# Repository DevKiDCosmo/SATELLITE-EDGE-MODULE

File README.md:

# SATELLITE-EDGE-MODULE
A satellite edge module ready for competition

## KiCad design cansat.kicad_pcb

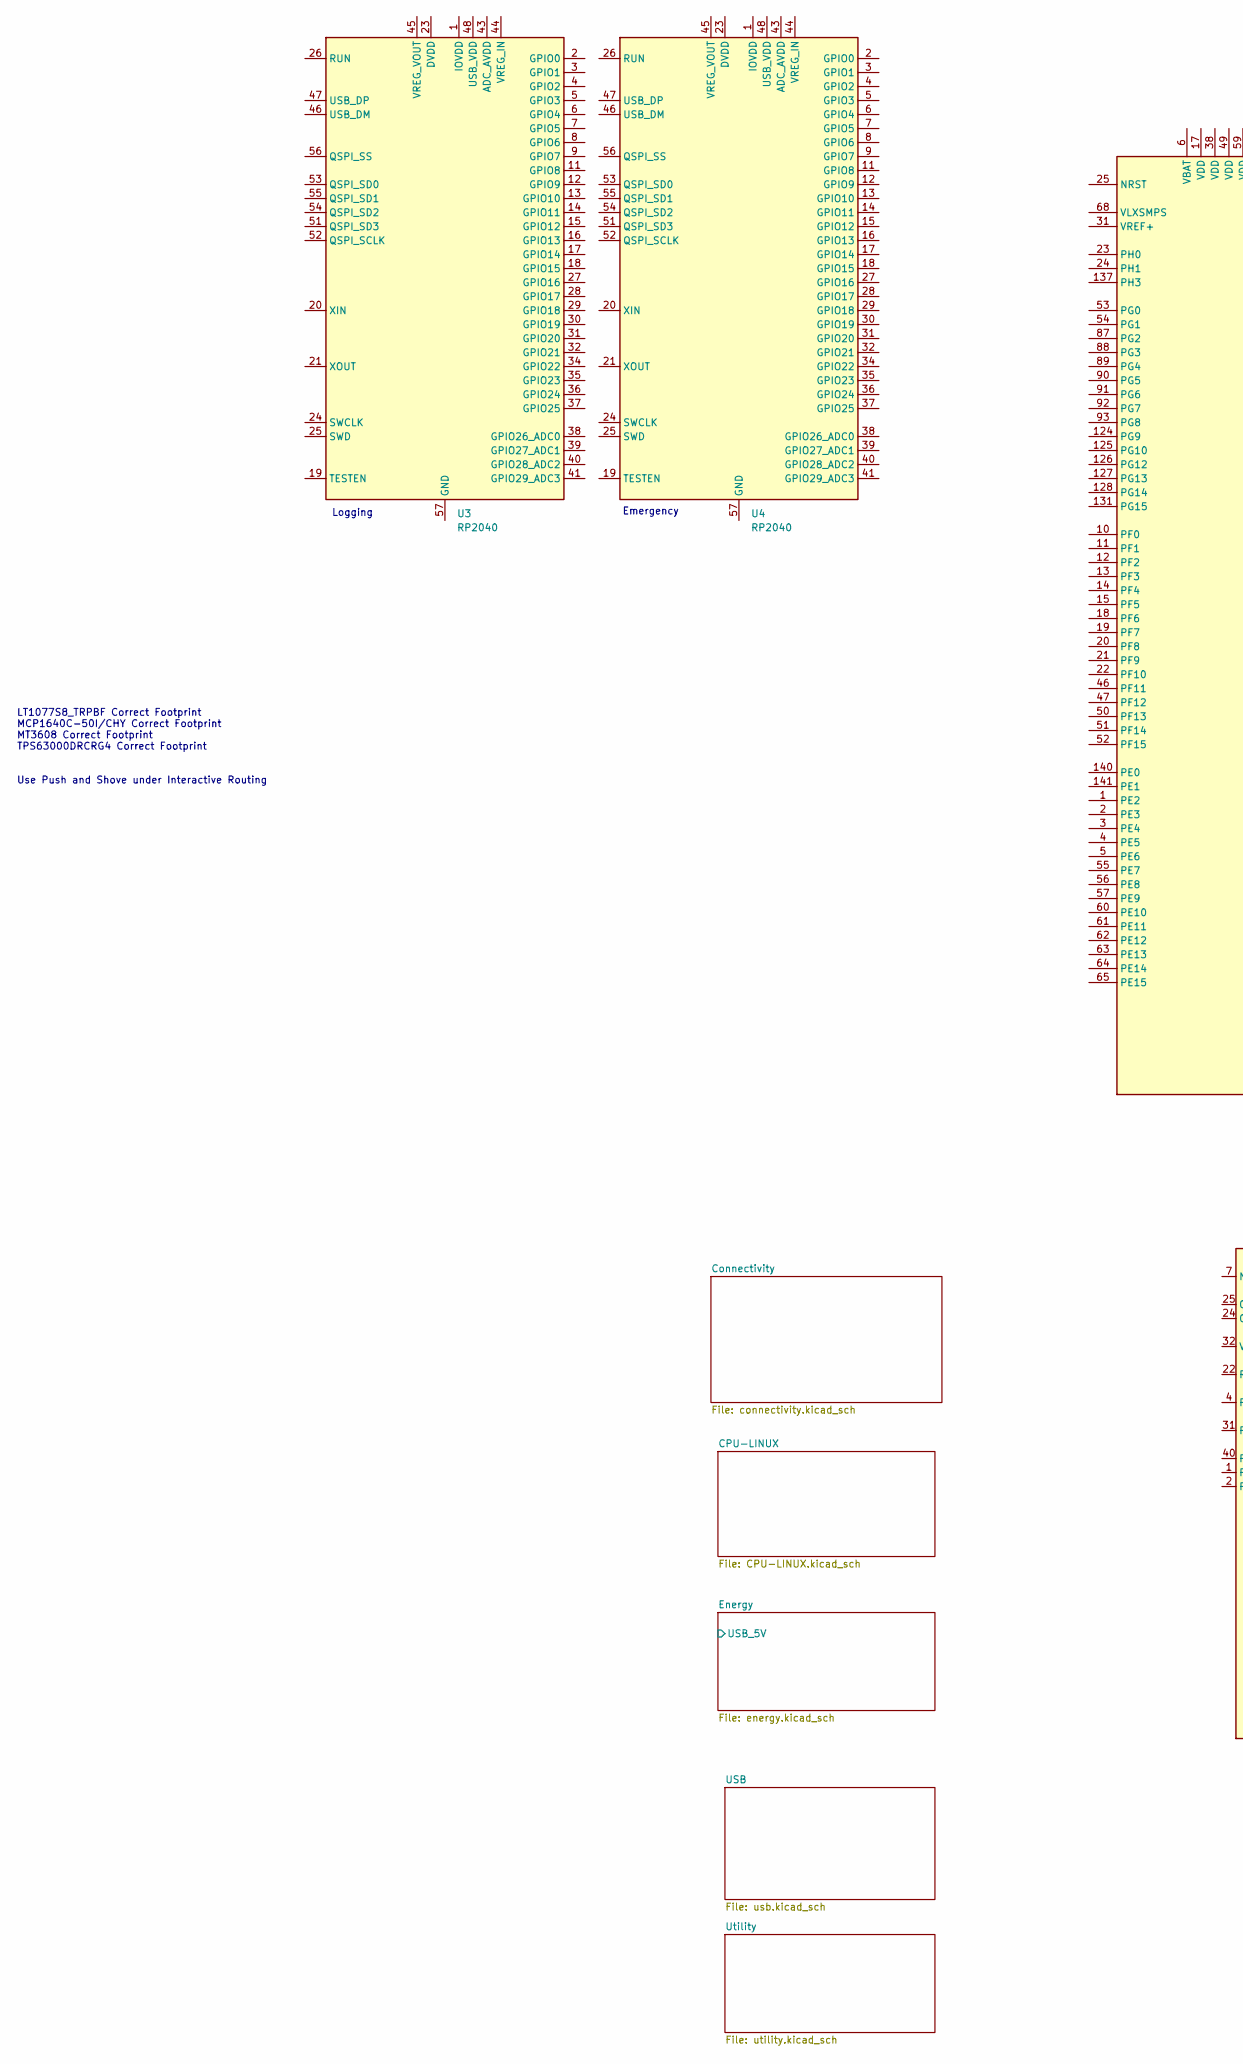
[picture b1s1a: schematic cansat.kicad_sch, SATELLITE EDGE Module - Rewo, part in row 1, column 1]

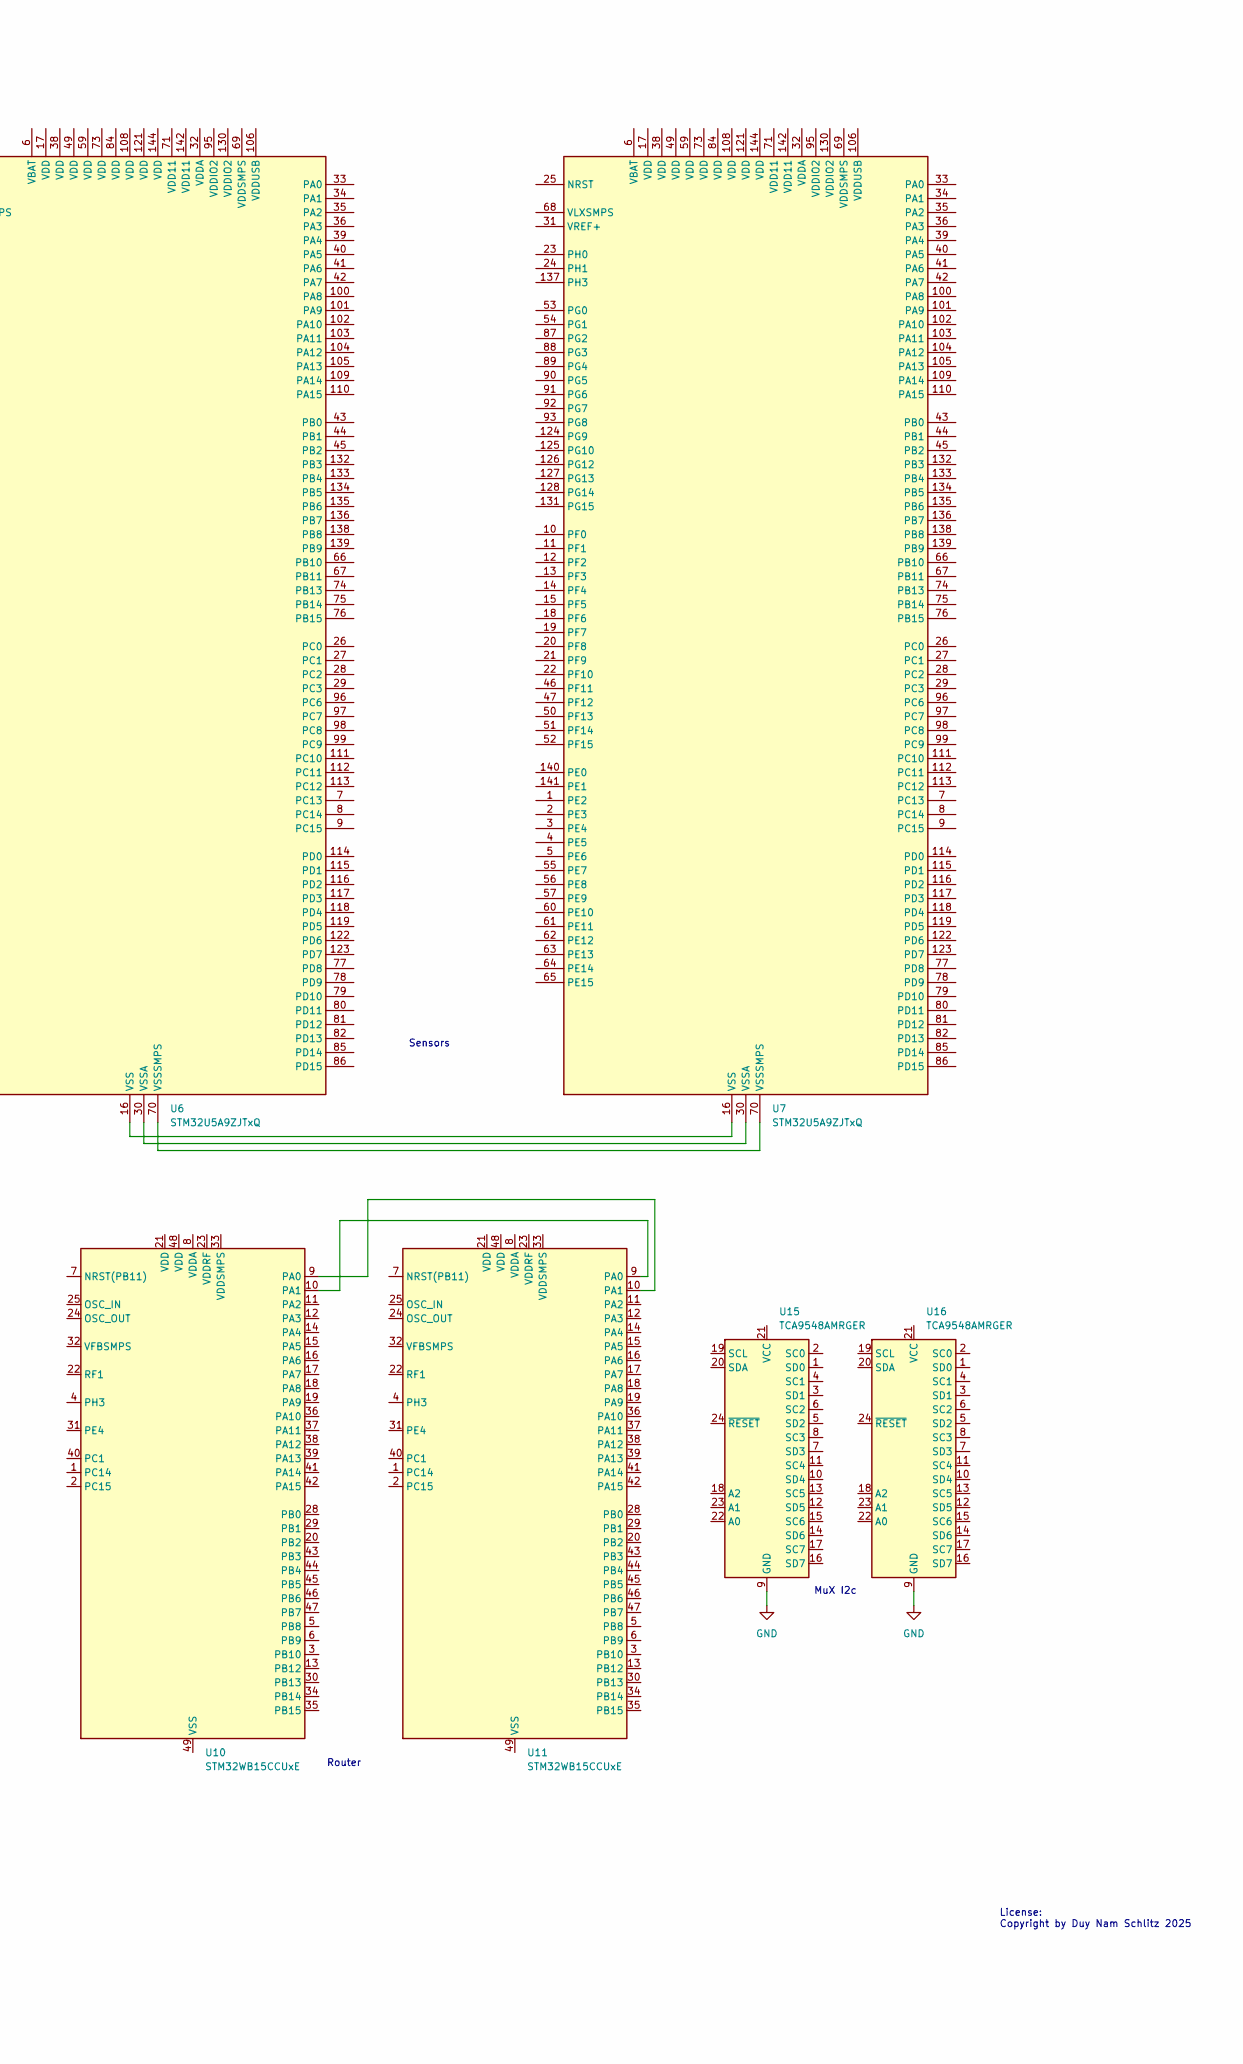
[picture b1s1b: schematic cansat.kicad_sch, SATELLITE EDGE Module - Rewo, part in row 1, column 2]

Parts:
U3, U4: RP2040; QFN-56-1EP_7x7mm_P0.4mm_EP3.2x3.2mm
U6, U7: STM32U5A9ZJTxQ; LQFP-144_20x20mm_P0.5mm
U10, U11: STM32WB15CCUxE; QFN-48-1EP_7x7mm_P0.5mm_EP5.6x5.6mm
U15, U16: TCA9548AMRGER; Texas_RGE0024C_VQFN-24-1EP_4x4mm_P0.5mm_EP2.1x2.1mm

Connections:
GND: U15.9 (GND), U16.9 (GND); also elsewhere on the board
unnamed: U3.23 (DVDD), U3.50 (DVDD)
unnamed: U3.1 (IOVDD), U3.10 (IOVDD), U3.22 (IOVDD), U3.33 (IOVDD), U3.42 (IOVDD), U3.49 (IOVDD)
unnamed: U4.23 (DVDD), U4.50 (DVDD)
unnamed: U4.1 (IOVDD), U4.10 (IOVDD), U4.22 (IOVDD), U4.33 (IOVDD), U4.42 (IOVDD), U4.49 (IOVDD)
unnamed: U6.16 (VSS), U6.37 (VSS), U6.48 (VSS), U6.58 (VSS), U6.72 (VSS), U6.83 (VSS), U6.94 (VSS), U6.107 (VSS), U6.120 (VSS), U6.129 (VSS), U6.143 (VSS), U7.16 (VSS), U7.37 (VSS), U7.48 (VSS), U7.58 (VSS), U7.72 (VSS), U7.83 (VSS), U7.94 (VSS), U7.107 (VSS), U7.120 (VSS), U7.129 (VSS), U7.143 (VSS)
unnamed: U6.30 (VSSA), U7.30 (VSSA)
unnamed: U6.70 (VSSSMPS), U7.70 (VSSSMPS)
unnamed: U10.9 (PA0), U11.10 (PA1)
unnamed: U10.10 (PA1), U11.9 (PA0)

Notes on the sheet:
Logging
Sensors
License: Copyright by Duy Nam Schlitz 2025
MuX I2c
LT1077S8_TRPBF Correct Footprint MCP1640C-50I/CHY Correct Footprint MT3608 Correct Footprint TPS63000DRCRG4 Correct Footprint Use Push and Shove under Interactive Routing
Router
Emergency

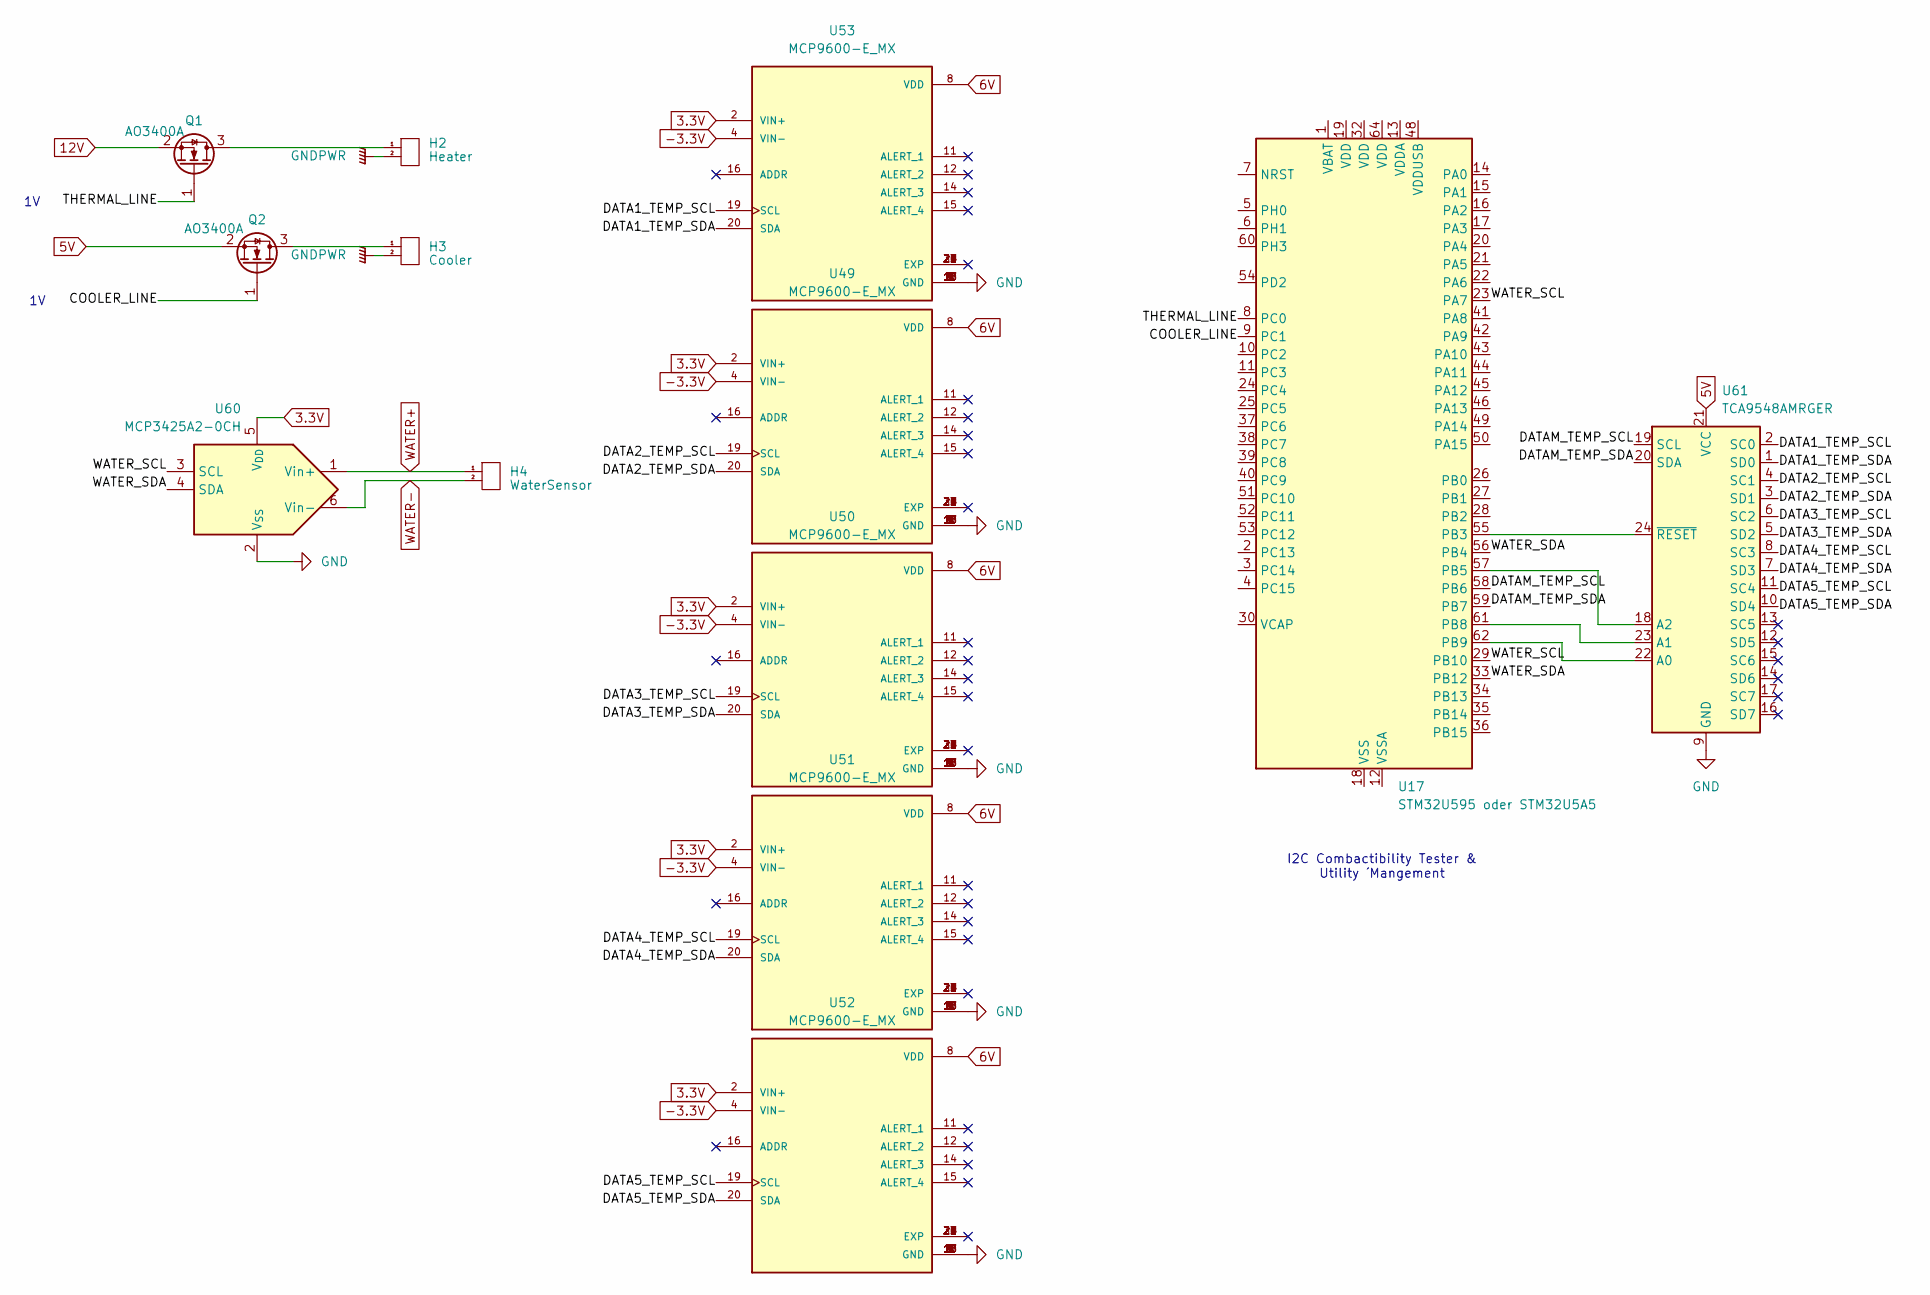
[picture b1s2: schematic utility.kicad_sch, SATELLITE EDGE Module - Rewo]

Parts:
H2: Heater; PinHeader_1x02_P2.54mm_Vertical
H3: Cooler; PinHeader_1x02_P2.54mm_Vertical
H4: WaterSensor; PinHeader_1x02_P2.54mm_Vertical
Q1, Q2: AO3400A; SOT-23
U17: STM32U595 oder STM32U5A5; LQFP-64_10x10mm_P0.5mm
U49, U50, U51, U52, U53: MCP9600-E_MX; QFN65P500X500X100-21N_MCP9600-E_MX; PARTREV F
U60: MCP3425A2-0CH; SOT-23-6
U61: TCA9548AMRGER; Texas_RGE0024C_VQFN-24-1EP_4x4mm_P0.5mm_EP2.1x2.1mm

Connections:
3.3V: U49.2 (VIN+), U50.2 (VIN+), U51.2 (VIN+), U52.2 (VIN+), U53.2 (VIN+), U60.5 (V_{DD}); also elsewhere on the board
5V: Q2.2 (S), U61.21 (VCC); also elsewhere on the board
6V: U49.8 (VDD), U50.8 (VDD), U51.8 (VDD), U52.8 (VDD), U53.8 (VDD); also elsewhere on the board
12V: Q1.2 (S); also elsewhere on the board
-3.3V: U49.4 (VIN-), U50.4 (VIN-), U51.4 (VIN-), U52.4 (VIN-), U53.4 (VIN-); also elsewhere on the board
/Utility/COOLER_LINE: Q2.1 (G), U17.9 (PC1)
/Utility/DATA1_TEMP_SCL: U53.19 (SCL), U61.2 (SC0)
/Utility/DATA1_TEMP_SDA: U53.20 (SDA), U61.1 (SD0)
/Utility/DATA2_TEMP_SCL: U49.19 (SCL), U61.4 (SC1)
/Utility/DATA2_TEMP_SDA: U49.20 (SDA), U61.3 (SD1)
/Utility/DATA3_TEMP_SCL: U50.19 (SCL), U61.6 (SC2)
/Utility/DATA3_TEMP_SDA: U50.20 (SDA), U61.5 (SD2)
/Utility/DATA4_TEMP_SCL: U51.19 (SCL), U61.8 (SC3)
/Utility/DATA4_TEMP_SDA: U51.20 (SDA), U61.7 (SD3)
/Utility/DATA5_TEMP_SCL: U52.19 (SCL), U61.11 (SC4)
/Utility/DATA5_TEMP_SDA: U52.20 (SDA), U61.10 (SD4)
/Utility/DATAM_TEMP_SCL: U17.58 (PB6), U61.19 (SCL)
/Utility/DATAM_TEMP_SDA: U17.59 (PB7), U61.20 (SDA)
/Utility/THERMAL_LINE: Q1.1 (G), U17.8 (PC0)
/Utility/WATER_SCL: U17.23 (PA7), U17.29 (PB10), U60.3 (SCL)
/Utility/WATER_SDA: U17.33 (PB12), U17.56 (PB4), U60.4 (SDA)
GND: U49.1 (GND), U49.3 (GND), U49.5 (GND), U49.6 (GND), U49.7 (GND), U49.9 (GND), U49.10 (GND), U49.13 (GND), U49.17 (GND), U49.18 (GND), U50.1 (GND), U50.3 (GND), U50.5 (GND), U50.6 (GND), U50.7 (GND), U50.9 (GND), U50.10 (GND), U50.13 (GND), U50.17 (GND), U50.18 (GND), U51.1 (GND), U51.3 (GND), U51.5 (GND), U51.6 (GND), U51.7 (GND), U51.9 (GND), U51.10 (GND), U51.13 (GND), U51.17 (GND), U51.18 (GND), U52.1 (GND), U52.3 (GND), U52.5 (GND), U52.6 (GND), U52.7 (GND), U52.9 (GND), U52.10 (GND), U52.13 (GND), U52.17 (GND), U52.18 (GND), U53.1 (GND), U53.3 (GND), U53.5 (GND), U53.6 (GND), U53.7 (GND), U53.9 (GND), U53.10 (GND), U53.13 (GND), U53.17 (GND), U53.18 (GND), U60.2 (V_{SS}), U61.9 (GND); also elsewhere on the board
GNDPWR: H2.2, H3.2; also elsewhere on the board
unnamed: H2.1, Q1.3 (D)
unnamed: H3.1, Q2.3 (D)
unnamed: U17.55 (PB3), U61.24 (~RESET)
unnamed: U17.57 (PB5), U61.18 (A2)
unnamed: U17.61 (PB8), U61.23 (A1)
unnamed: U17.62 (PB9), U61.22 (A0)
unnamed: U17.18 (VSS), U17.31 (VSS), U17.47 (VSS), U17.63 (VSS)
WATER+: H4.1, U60.1 (Vin+); also elsewhere on the board
WATER-: H4.2, U60.6 (Vin-); also elsewhere on the board

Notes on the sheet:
I2C Combactibility Tester & Utility ´Mangement

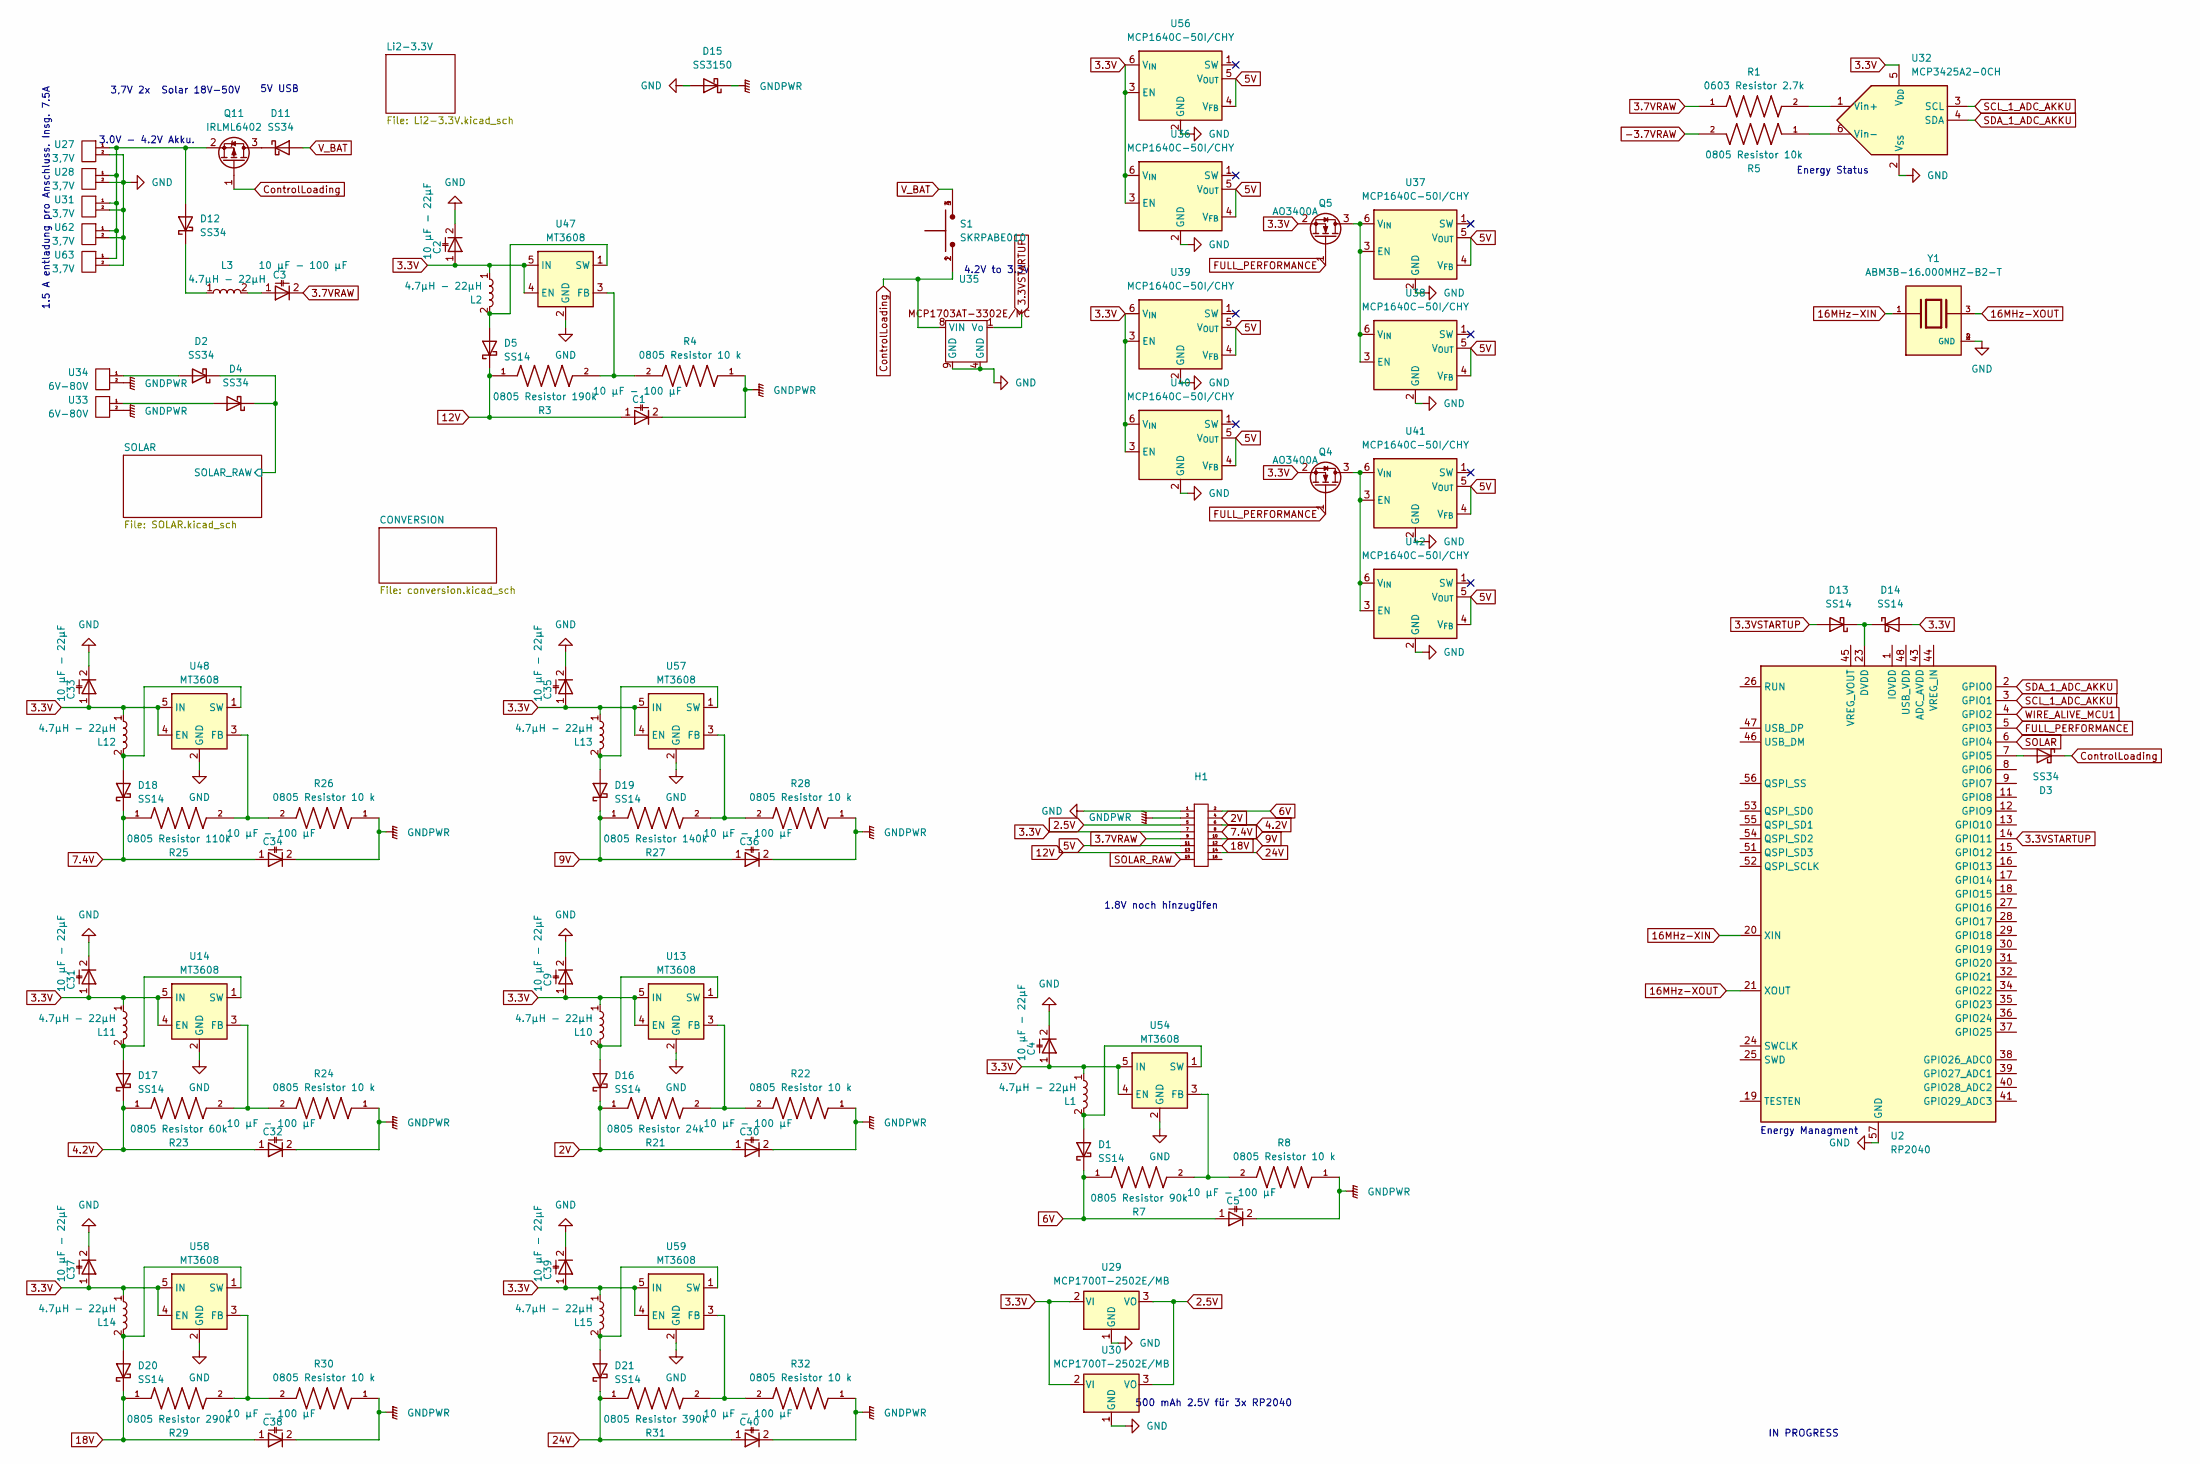
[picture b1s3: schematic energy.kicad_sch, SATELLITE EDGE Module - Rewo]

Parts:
C1, C3, C5, C30, C32, C34, C36, C38, C40: 10 µF - 100 µF; C_0603_1608Metric
C2, C4, C9, C31, C33, C35, C37, C39: 10 µF - 22µF; C_0603_1608Metric
D1, D5, D13, D14, D16, D17, D18, D19, D20, D21: SS14; D_SMA
D2, D3, D4, D11, D12: SS34; D_SMA
D15: SS3150; D_SMA
H1: PinHeader_2x08_P2.54mm_Vertical
L1, L2, L3, L10, L11, L12, L13, L14, L15: 4.7µH - 22µH; L_0805_2012Metric
Q4, Q5: AO3400A; SOT-23
Q11: IRLML6402; SOT-23
R1: 0603 Resistor 2.7k; R_0201_0603Metric
R3: 0805 Resistor 190k; R_0805_2012Metric
R4, R8, R22, R24, R26, R28, R30, R32: 0805 Resistor 10 k; R_0805_2012Metric
R5: 0805 Resistor 10k; R_0805_2012Metric
R7: 0805 Resistor 90k; R_0805_2012Metric
R21: 0805 Resistor 24k; R_0805_2012Metric
R23: 0805 Resistor 60k; R_0805_2012Metric
R25: 0805 Resistor 110k; R_0805_2012Metric
R27: 0805 Resistor 140k; R_0805_2012Metric
R29: 0805 Resistor 290k; R_0805_2012Metric
R31: 0805 Resistor 390k; R_0805_2012Metric
S1: SKRPABE010; SW_SKRPABE010
U2: RP2040; QFN-56-1EP_7x7mm_P0.4mm_EP3.2x3.2mm
U13, U14, U47, U48, U54, U57, U58, U59: MT3608; SOT-23-6
U27, U28, U31, U62, U63: 3,7V; JST_PH_B2B-PH-K_1x02_P2.00mm_Vertical
U29, U30: MCP1700T-2502E/MB; SOT-89-3
U32: MCP3425A2-0CH; SOT-23-6
U33, U34: 6V-80V; JST_PH_B2B-PH-K_1x02_P2.00mm_Vertical
U35: SON50P200X300X100-9N
U36, U37, U38, U39, U40, U41, U42, U56: MCP1640C-50I/CHY; SOT-23-6
Y1: ABM3B-16.000MHZ-B2-T; XTAL_ABM3B-16.000MHZ-B2-T; PARTREV 08.25.15

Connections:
2.5V: H1.5, U29.3 (VO), U30.3 (VO); also elsewhere on the board
2V: C30.1, D16.1 (K), H1.4, R21.1; also elsewhere on the board
3.3V: C2.1, C4.1, C9.1, C31.1, C33.1, C35.1, C37.1, C39.1, D14.2 (A), H1.7, L1.1, L2.1, L10.1, L11.1, L12.1, L13.1, L14.1, L15.1, Q4.2 (S), Q5.2 (S), U13.4 (EN), U13.5 (IN), U14.4 (EN), U14.5 (IN), U29.2 (VI), U30.2 (VI), U32.5 (V_{DD}), U36.3 (EN), U36.6 (V_{IN}), U39.3 (EN), U39.6 (V_{IN}), U40.3 (EN), U40.6 (V_{IN}), U47.4 (EN), U47.5 (IN), U48.4 (EN), U48.5 (IN), U54.4 (EN), U54.5 (IN), U56.3 (EN), U56.6 (V_{IN}), U57.4 (EN), U57.5 (IN), U58.4 (EN), U58.5 (IN), U59.4 (EN), U59.5 (IN); also elsewhere on the board
3.3VSTARTUP: D13.2 (A), U2.14 (GPIO11), U35.1 (Vo)
3.7VRAW: C3.2, H1.9, R1.1; also elsewhere on the board
4.2V: C32.1, D17.1 (K), H1.6, R23.1; also elsewhere on the board
5V: H1.11, U36.4 (V_{FB}), U36.5 (V_{OUT}), U37.4 (V_{FB}), U37.5 (V_{OUT}), U38.4 (V_{FB}), U38.5 (V_{OUT}), U39.4 (V_{FB}), U39.5 (V_{OUT}), U40.4 (V_{FB}), U40.5 (V_{OUT}), U41.4 (V_{FB}), U41.5 (V_{OUT}), U42.4 (V_{FB}), U42.5 (V_{OUT}), U56.4 (V_{FB}), U56.5 (V_{OUT}); also elsewhere on the board
6V: C5.1, D1.1 (K), H1.2, R7.1; also elsewhere on the board
7.4V: C34.1, D18.1 (K), H1.8, R25.1; also elsewhere on the board
9V: C36.1, D19.1 (K), H1.10, R27.1; also elsewhere on the board
12V: C1.1, D5.1 (K), H1.13, R3.1; also elsewhere on the board
16MHz-XIN: U2.20 (XIN), Y1.1
16MHz-XOUT: U2.21 (XOUT), Y1.3
18V: C38.1, D20.1 (K), H1.12, R29.1; also elsewhere on the board
24V: C40.1, D21.1 (K), H1.14, R31.1; also elsewhere on the board
-3.7VRAW: R5.2; also elsewhere on the board
/Energy/SOLAR/SOLAR_RAW: D2.1 (K), D4.1 (K); also elsewhere on the board
ControlLoading: D3.1 (K), Q11.1 (G), S1.1, S1.2, U35.8 (VIN)
FULL_PERFORMANCE: Q4.1 (G), Q5.1 (G), U2.5 (GPIO3); also elsewhere on the board
GND: C2.2, C4.2, C9.2, C31.2, C33.2, C35.2, C37.2, C39.2, D15.2 (A), H1.1, U2.57 (GND), U13.2 (GND), U14.2 (GND), U27.2, U28.2, U29.1 (GND), U30.1 (GND), U31.2, U32.2 (V_{SS}), U35.4 (GND), U35.9 (GND), U36.2 (GND), U37.2 (GND), U38.2 (GND), U39.2 (GND), U40.2 (GND), U41.2 (GND), U42.2 (GND), U47.2 (GND), U48.2 (GND), U54.2 (GND), U56.2 (GND), U57.2 (GND), U58.2 (GND), U59.2 (GND), U62.2, U63.2, Y1.2 (GND), Y1.4 (GND); also elsewhere on the board
GNDPWR: C1.2, C5.2, C30.2, C32.2, C34.2, C36.2, C38.2, C40.2, D15.1 (K), H1.3, R4.1, R8.1, R22.1, R24.1, R26.1, R28.1, R30.1, R32.1, U33.2, U34.2; also elsewhere on the board
unnamed: C3.1, L3.2
unnamed: D1.2 (A), L1.2, U54.1 (SW)
unnamed: D2.2 (A), U34.1
unnamed: D3.2 (A), U2.7 (GPIO5)
unnamed: D4.2 (A), U33.1
unnamed: D5.2 (A), L2.2, U47.1 (SW)
unnamed: D11.1 (K), Q11.3 (D)
unnamed: D12.2 (A), Q11.2 (S), U27.1, U28.1, U31.1, U62.1, U63.1
unnamed: D12.1 (K), L3.1
unnamed: D13.1 (K), D14.1 (K), U2.23 (DVDD), U2.50 (DVDD)
unnamed: D16.2 (A), L10.2, U13.1 (SW)
unnamed: D17.2 (A), L11.2, U14.1 (SW)
unnamed: D18.2 (A), L12.2, U48.1 (SW)
unnamed: D19.2 (A), L13.2, U57.1 (SW)
unnamed: D20.2 (A), L14.2, U58.1 (SW)
unnamed: D21.2 (A), L15.2, U59.1 (SW)
unnamed: Q4.3 (D), U41.3 (EN), U41.6 (V_{IN}), U42.3 (EN), U42.6 (V_{IN})
unnamed: Q5.3 (D), U37.3 (EN), U37.6 (V_{IN}), U38.3 (EN), U38.6 (V_{IN})
unnamed: U2.1 (IOVDD), U2.10 (IOVDD), U2.22 (IOVDD), U2.33 (IOVDD), U2.42 (IOVDD), U2.49 (IOVDD)
unnamed: R21.2, R22.2, U13.3 (FB)
unnamed: R23.2, R24.2, U14.3 (FB)
unnamed: R1.2, U32.1 (Vin+)
unnamed: R5.1, U32.6 (Vin-)
unnamed: R3.2, R4.2, U47.3 (FB)
unnamed: R25.2, R26.2, U48.3 (FB)
unnamed: R7.2, R8.2, U54.3 (FB)
unnamed: R27.2, R28.2, U57.3 (FB)
unnamed: R29.2, R30.2, U58.3 (FB)
unnamed: R31.2, R32.2, U59.3 (FB)
SCL_1_ADC_AKKU: U2.3 (GPIO1), U32.3 (SCL)
SDA_1_ADC_AKKU: U2.2 (GPIO0), U32.4 (SDA)
SOLAR: U2.6 (GPIO4); also elsewhere on the board
SOLAR_RAW: H1.15; also elsewhere on the board
V_BAT: D11.2 (A), S1.3, S1.4; also elsewhere on the board
WIRE_ALIVE_MCU1: U2.4 (GPIO2)

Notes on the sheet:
1.5 A entladung pro Anschluss. Insg. 7.5A
4.2V to 3.3V
3.0V - 4.2V Akku.
500 mAh 2.5V für 3x RP2040
3,7V 2x
IN PROGRESS
5V USB
Energy Status
1.8V noch hinzugüfen
Energy Managment
Solar 18V-50V

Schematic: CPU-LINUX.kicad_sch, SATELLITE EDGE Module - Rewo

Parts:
J2, J3, J4, J5, J6, J7, J8, J9: ADM6-60-X-X-4-X-A-X; SAMTEC_ADM6-60-X-X-4-X-A-X; PARTREV C
U20: STM32MP157AABx; ST_LFBGA-354_16x16mm_Layout19x19_P0.8mm
U21, U22: MT40A512M16JY; Micron_FBGA-96_8x14mm_Layout9x16_P0.8mm
U23, U24: MT41K256M16LY; Micron_FBGA-96_7.5x13.5mm_Layout9x16_P0.8mm
U25: RK3566; IC_RK3566; PARTREV 1.1
U26: S32G274AABK0VUCT; IC_S32G274AABK0VUCT; PARTREV 6

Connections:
2.5V: J2.A06, J4.A04; also elsewhere on the board
2V: J2.A13, J4.A11; also elsewhere on the board
3.3V: J2.A07, J4.A05; also elsewhere on the board
3.7VRAW: J2.A08, J4.A06; also elsewhere on the board
4.2V: J2.A14; also elsewhere on the board
5V: J2.A09, J4.A07; also elsewhere on the board
6V: J2.A12, J4.A10; also elsewhere on the board
7.4V: J2.A15; also elsewhere on the board
9V: J2.A16; also elsewhere on the board
12V: J2.A10, J4.A08; also elsewhere on the board
18V: J2.A17; also elsewhere on the board
24V: J2.A18; also elsewhere on the board
GND: J2.A03, J2.A04, J2.B03, J2.C03, J2.D03, J4.A01, J4.A02; also elsewhere on the board
GNDPWR: J2.A05, J4.A03; also elsewhere on the board
unnamed: U20.A1 (VSS), U20.A19 (VSS), U20.B2 (VSS), U20.B6 (VSS), U20.C3 (VSS), U20.C17 (VSS), U20.D1 (VSS), U20.D4 (VSS), U20.D5 (VSS), U20.D8 (VSS), U20.E2 (VSS), U20.E4 (VSS), U20.E5 (VSS), U20.E6 (VSS), U20.E8 (VSS), U20.E10 (VSS), U20.E12 (VSS), U20.E14 (VSS), U20.E16 (VSS), U20.F5 (VSS), U20.F7 (VSS), U20.F9 (VSS), U20.F11 (VSS), U20.F15 (VSS), U20.G2 (VSS), U20.G4 (VSS), U20.G6 (VSS), U20.G8 (VSS), U20.G10 (VSS), U20.G12 (VSS), U20.G14 (VSS), U20.H5 (VSS), U20.H7 (VSS), U20.H9 (VSS), U20.H11 (VSS), U20.H13 (VSS), U20.H15 (VSS), U20.J3 (VSS), U20.J6 (VSS), U20.J8 (VSS), U20.J10 (VSS), U20.J12 (VSS), U20.J14 (VSS), U20.K2 (VSS), U20.K5 (VSS), U20.K7 (VSS), U20.K9 (VSS), U20.K11 (VSS), U20.K13 (VSS), U20.K15 (VSS), U20.L6 (VSS), U20.L8 (VSS), U20.L10 (VSS), U20.L12 (VSS), U20.L14 (VSS), U20.M5 (VSS), U20.M7 (VSS), U20.M9 (VSS), U20.M11 (VSS), U20.M13 (VSS), U20.M15 (VSS), U20.N6 (VSS), U20.N8 (VSS), U20.N10 (VSS), U20.N12 (VSS), U20.N14 (VSS), U20.P7 (VSS), U20.P9 (VSS), U20.P11 (VSS), U20.P13 (VSS), U20.P15 (VSS), U20.R2 (VSS), U20.R6 (VSS), U20.R8 (VSS), U20.R10 (VSS), U20.R12 (VSS), U20.R14 (VSS), U20.R16 (VSS), U20.T4 (VSS), U20.U3 (VSS), U20.U6 (VSS), U20.U8 (VSS), U20.U17 (VSS), U20.W1 (VSS), U20.W19 (VSS)
unnamed: U20.N4 (VSSA), U20.P5 (VSSA), U20.R5 (VSSA)
unnamed: U20.C12 (VSS_DSI), U20.C13 (VSS_DSI), U20.C14 (VSS_DSI), U20.C15 (VSS_DSI), U20.C16 (VSS_DSI)
unnamed: U20.U13 (VSS_USBHS), U20.U14 (VSS_USBHS), U20.V12 (VSS_USBHS), U20.V15 (VSS_USBHS)
unnamed: U21.A1 (V_{DDQ}), U21.A9 (V_{DDQ}), U21.C1 (V_{DDQ}), U21.D9 (V_{DDQ}), U21.F2 (V_{DDQ}), U21.F8 (V_{DDQ}), U21.G1 (V_{DDQ}), U21.G9 (V_{DDQ}), U21.J2 (V_{DDQ}), U21.J8 (V_{DDQ})
unnamed: U21.B3 (V_{DD}), U21.B9 (V_{DD}), U21.D1 (V_{DD}), U21.G7 (V_{DD}), U21.J1 (V_{DD}), U21.J9 (V_{DD}), U21.L1 (V_{DD}), U21.L9 (V_{DD}), U21.R1 (V_{DD}), U21.T9 (V_{DD})
unnamed: U21.B1 (V_{PP}), U21.R9 (V_{PP})
unnamed: U21.A2 (V_{SSQ}), U21.A8 (V_{SSQ}), U21.C9 (V_{SSQ}), U21.D2 (V_{SSQ}), U21.D8 (V_{SSQ}), U21.E3 (V_{SSQ}), U21.E8 (V_{SSQ}), U21.F1 (V_{SSQ}), U21.H1 (V_{SSQ}), U21.H9 (V_{SSQ})
unnamed: U21.B2 (V_{SS}), U21.E1 (V_{SS}), U21.E9 (V_{SS}), U21.G8 (V_{SS}), U21.K1 (V_{SS}), U21.K9 (V_{SS}), U21.M9 (V_{SS}), U21.N1 (V_{SS}), U21.T1 (V_{SS})
unnamed: U22.A1 (V_{DDQ}), U22.A9 (V_{DDQ}), U22.C1 (V_{DDQ}), U22.D9 (V_{DDQ}), U22.F2 (V_{DDQ}), U22.F8 (V_{DDQ}), U22.G1 (V_{DDQ}), U22.G9 (V_{DDQ}), U22.J2 (V_{DDQ}), U22.J8 (V_{DDQ})
unnamed: U22.B3 (V_{DD}), U22.B9 (V_{DD}), U22.D1 (V_{DD}), U22.G7 (V_{DD}), U22.J1 (V_{DD}), U22.J9 (V_{DD}), U22.L1 (V_{DD}), U22.L9 (V_{DD}), U22.R1 (V_{DD}), U22.T9 (V_{DD})
unnamed: U22.B1 (V_{PP}), U22.R9 (V_{PP})
unnamed: U22.A2 (V_{SSQ}), U22.A8 (V_{SSQ}), U22.C9 (V_{SSQ}), U22.D2 (V_{SSQ}), U22.D8 (V_{SSQ}), U22.E3 (V_{SSQ}), U22.E8 (V_{SSQ}), U22.F1 (V_{SSQ}), U22.H1 (V_{SSQ}), U22.H9 (V_{SSQ})
unnamed: U22.B2 (V_{SS}), U22.E1 (V_{SS}), U22.E9 (V_{SS}), U22.G8 (V_{SS}), U22.K1 (V_{SS}), U22.K9 (V_{SS}), U22.M9 (V_{SS}), U22.N1 (V_{SS}), U22.T1 (V_{SS})
unnamed: U23.A1 (V_{DDQ}), U23.A8 (V_{DDQ}), U23.C1 (V_{DDQ}), U23.C9 (V_{DDQ}), U23.D2 (V_{DDQ}), U23.E9 (V_{DDQ}), U23.F1 (V_{DDQ}), U23.H2 (V_{DDQ}), U23.H9 (V_{DDQ})
unnamed: U23.B2 (V_{DD}), U23.D9 (V_{DD}), U23.G7 (V_{DD}), U23.K2 (V_{DD}), U23.K8 (V_{DD}), U23.N1 (V_{DD}), U23.N9 (V_{DD}), U23.R1 (V_{DD}), U23.R9 (V_{DD})
unnamed: U23.B1 (V_{SSQ}), U23.B9 (V_{SSQ}), U23.D1 (V_{SSQ}), U23.D8 (V_{SSQ}), U23.E2 (V_{SSQ}), U23.E8 (V_{SSQ}), U23.F9 (V_{SSQ}), U23.G1 (V_{SSQ}), U23.G9 (V_{SSQ})
unnamed: U23.A9 (V_{SS}), U23.B3 (V_{SS}), U23.E1 (V_{SS}), U23.G8 (V_{SS}), U23.J2 (V_{SS}), U23.J8 (V_{SS}), U23.M1 (V_{SS}), U23.M9 (V_{SS}), U23.P1 (V_{SS}), U23.P9 (V_{SS}), U23.T1 (V_{SS}), U23.T9 (V_{SS})
unnamed: U24.A1 (V_{DDQ}), U24.A8 (V_{DDQ}), U24.C1 (V_{DDQ}), U24.C9 (V_{DDQ}), U24.D2 (V_{DDQ}), U24.E9 (V_{DDQ}), U24.F1 (V_{DDQ}), U24.H2 (V_{DDQ}), U24.H9 (V_{DDQ})
unnamed: U24.B2 (V_{DD}), U24.D9 (V_{DD}), U24.G7 (V_{DD}), U24.K2 (V_{DD}), U24.K8 (V_{DD}), U24.N1 (V_{DD}), U24.N9 (V_{DD}), U24.R1 (V_{DD}), U24.R9 (V_{DD})
unnamed: U24.B1 (V_{SSQ}), U24.B9 (V_{SSQ}), U24.D1 (V_{SSQ}), U24.D8 (V_{SSQ}), U24.E2 (V_{SSQ}), U24.E8 (V_{SSQ}), U24.F9 (V_{SSQ}), U24.G1 (V_{SSQ}), U24.G9 (V_{SSQ})
unnamed: U24.A9 (V_{SS}), U24.B3 (V_{SS}), U24.E1 (V_{SS}), U24.G8 (V_{SS}), U24.J2 (V_{SS}), U24.J8 (V_{SS}), U24.M1 (V_{SS}), U24.M9 (V_{SS}), U24.P1 (V_{SS}), U24.P9 (V_{SS}), U24.T1 (V_{SS}), U24.T9 (V_{SS})
unnamed: U26.J8 (VDD1), U26.J10 (VDD1), U26.J12 (VDD1), U26.J14 (VDD1), U26.J16 (VDD1), U26.K11 (VDD1), U26.K13 (VDD1), U26.K15 (VDD1), U26.L8 (VDD1), U26.L10 (VDD1), U26.L12 (VDD1), U26.L14 (VDD1), U26.M9 (VDD1), U26.M11 (VDD1), U26.M13 (VDD1)
unnamed: U26.M15 (VDD2), U26.N8 (VDD2), U26.N10 (VDD2), U26.N12 (VDD2), U26.N14 (VDD2), U26.N16 (VDD2), U26.P9 (VDD2), U26.P11 (VDD2), U26.P13 (VDD2), U26.P15 (VDD2), U26.R8 (VDD2), U26.R10 (VDD2), U26.R12 (VDD2), U26.R14 (VDD2), U26.R16 (VDD2)
unnamed: U26.T8 (VDD_IO_A), U26.T9 (VDD_IO_A)
unnamed: U26.T11 (VDD_IO_AUR), U26.T12 (VDD_IO_AUR)
unnamed: U26.H9 (VDD_IO_B), U26.H10 (VDD_IO_B)
unnamed: U26.D4 (VDD_IO_DDR0_1), U26.F4 (VDD_IO_DDR0_1), U26.H4 (VDD_IO_DDR0_1), U26.H7 (VDD_IO_DDR0_1), U26.J7 (VDD_IO_DDR0_1), U26.K4 (VDD_IO_DDR0_1), U26.K7 (VDD_IO_DDR0_1), U26.L7 (VDD_IO_DDR0_1), U26.M4 (VDD_IO_DDR0_1), U26.M7 (VDD_IO_DDR0_1), U26.N7 (VDD_IO_DDR0_1), U26.P4 (VDD_IO_DDR0_1), U26.P7 (VDD_IO_DDR0_1), U26.T4 (VDD_IO_DDR0_1), U26.V4 (VDD_IO_DDR0_1)
unnamed: U26.P17 (VDD_IO_GMAC1), U26.R17 (VDD_IO_GMAC1)
unnamed: U26.T16 (VDD_IO_PCIE0), U26.U16 (VDD_IO_PCIE0)
unnamed: U26.T17 (VDD_IO_PCIE1), U26.U17 (VDD_IO_PCIE1)
unnamed: U26.H12 (VDD_STBY), U26.H13 (VDD_STBY)
unnamed: U26.T14 (VDD_VP_PCIE0), U26.U14 (VDD_VP_PCIE0)
unnamed: U26.T15 (VDD_VP_PCIE1), U26.U15 (VDD_VP_PCIE1)
unnamed: U26.A2 (VSS1), U26.B1 (VSS1), U26.B4 (VSS1), U26.B7 (VSS1), U26.B10 (VSS1), U26.B14 (VSS1), U26.C5 (VSS1), U26.C12 (VSS1), U26.D2 (VSS1), U26.D6 (VSS1), U26.D9 (VSS1), U26.E15 (VSS1), U26.E18 (VSS1), U26.F2 (VSS1), U26.F6 (VSS1)
unnamed: U26.F9 (VSS2), U26.F12 (VSS2), U26.G20 (VSS2), U26.H2 (VSS2), U26.H6 (VSS2), U26.J9 (VSS2), U26.J11 (VSS2), U26.J13 (VSS2), U26.J15 (VSS2), U26.J18 (VSS2), U26.J20 (VSS2), U26.J22 (VSS2), U26.K2 (VSS2), U26.K6 (VSS2), U26.K10 (VSS2)
unnamed: U26.K12 (VSS3), U26.K14 (VSS3), U26.K16 (VSS3), U26.L5 (VSS3), U26.L9 (VSS3), U26.L11 (VSS3), U26.L13 (VSS3), U26.L15 (VSS3), U26.M2 (VSS3), U26.M6 (VSS3), U26.M8 (VSS3), U26.M10 (VSS3), U26.M12 (VSS3), U26.M14 (VSS3), U26.M16 (VSS3)
unnamed: U26.AC22 (VSS4), U26.M18 (VSS4), U26.M20 (VSS4), U26.M22 (VSS4), U26.N9 (VSS4), U26.N11 (VSS4), U26.N13 (VSS4), U26.N15 (VSS4), U26.P2 (VSS4), U26.P6 (VSS4), U26.P8 (VSS4), U26.P10 (VSS4), U26.P12 (VSS4), U26.P14 (VSS4), U26.P16 (VSS4)
unnamed: U26.AB7 (VSS5), U26.AB10 (VSS5), U26.AB12 (VSS5), U26.AB14 (VSS5), U26.AB17 (VSS5), U26.AB20 (VSS5), U26.AB23 (VSS5), U26.AC2 (VSS5), U26.AC4 (VSS5), U26.AC7 (VSS5), U26.AC10 (VSS5), U26.AC12 (VSS5), U26.AC14 (VSS5), U26.AC17 (VSS5), U26.AC20 (VSS5)
unnamed: U26.AA5 (VSS6), U26.AA6 (VSS6), U26.AA8 (VSS6), U26.AA9 (VSS6), U26.AA11 (VSS6), U26.AA13 (VSS6), U26.AA15 (VSS6), U26.AA16 (VSS6), U26.AA18 (VSS6), U26.AA19 (VSS6), U26.AA21 (VSS6), U26.AA23 (VSS6), U26.AB1 (VSS6), U26.AB4 (VSS6), U26.Y22 (VSS6)
unnamed: U26.V10 (VSS7), U26.V12 (VSS7), U26.V15 (VSS7), U26.V16 (VSS7), U26.V18 (VSS7), U26.V19 (VSS7), U26.V22 (VSS7), U26.W14 (VSS7), U26.W17 (VSS7), U26.W20 (VSS7), U26.Y2 (VSS7), U26.Y6 (VSS7), U26.Y14 (VSS7), U26.Y17 (VSS7), U26.Y20 (VSS7)
unnamed: U26.R7 (VSS8), U26.R9 (VSS8), U26.R11 (VSS8), U26.R13 (VSS8), U26.R15 (VSS8), U26.R18 (VSS8), U26.R20 (VSS8), U26.R22 (VSS8), U26.T2 (VSS8), U26.T6 (VSS8), U26.V2 (VSS8), U26.V6 (VSS8), U26.V8 (VSS8)
unnamed: U26.A18 (VSS_ADC), U26.B19 (VSS_ADC), U26.C20 (VSS_ADC), U26.D21 (VSS_ADC), U26.E21 (VSS_ADC), U26.F22 (VSS_ADC), U26.G18 (VSS_ADC), U26.G23 (VSS_ADC)
unnamed: U26.A16 (VSS_FXOSC), U26.B17 (VSS_FXOSC), U26.C18 (VSS_FXOSC), U26.G14 (VSS_FXOSC)
SOLAR_RAW: J2.A11, J4.A09; also elsewhere on the board
WATER+: J2.A01; also elsewhere on the board
WATER-: J2.A02; also elsewhere on the board

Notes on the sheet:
Debug Pins
